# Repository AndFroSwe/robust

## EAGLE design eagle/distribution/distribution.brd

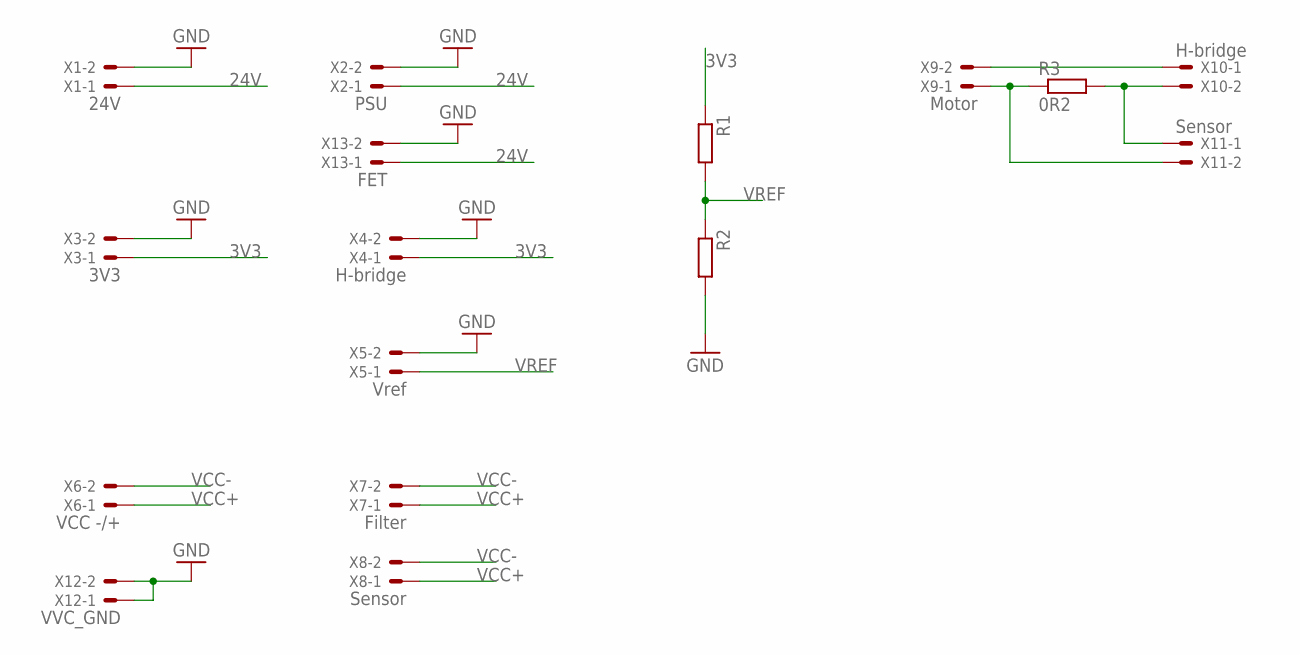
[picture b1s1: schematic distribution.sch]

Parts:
R1, R2: R-EU_0207/10; 0207/10
R3: 0R2; 0414/15
X1: 24V; 22-23-2021
X2: PSU; 22-23-2021
X3: 3V3; 22-23-2021
X4, X10: H-bridge; 22-23-2021
X5: Vref; 22-23-2021
X6: VCC -/+; 22-23-2021
X7: Filter; 22-23-2021
X8, X11: Sensor; 22-23-2021
X9: Motor; 22-23-2021
X12: VVC_GND; 22-23-2021
X13: FET; 22-23-2021

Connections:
3V3: R1.1, X3.1, X4.1
24V: X1.1, X2.1, X13.1
GND: R2.2, X1.2, X2.2, X3.2, X4.2, X5.2, X12.1, X12.2, X13.2
unnamed: R3.1, X9.1, X11.2
unnamed: R3.2, X10.2, X11.1
unnamed: X9.2, X10.1
VCC+: X6.1, X7.1, X8.1
VCC-: X6.2, X7.2, X8.2
VREF: R1.2, R2.1, X5.1

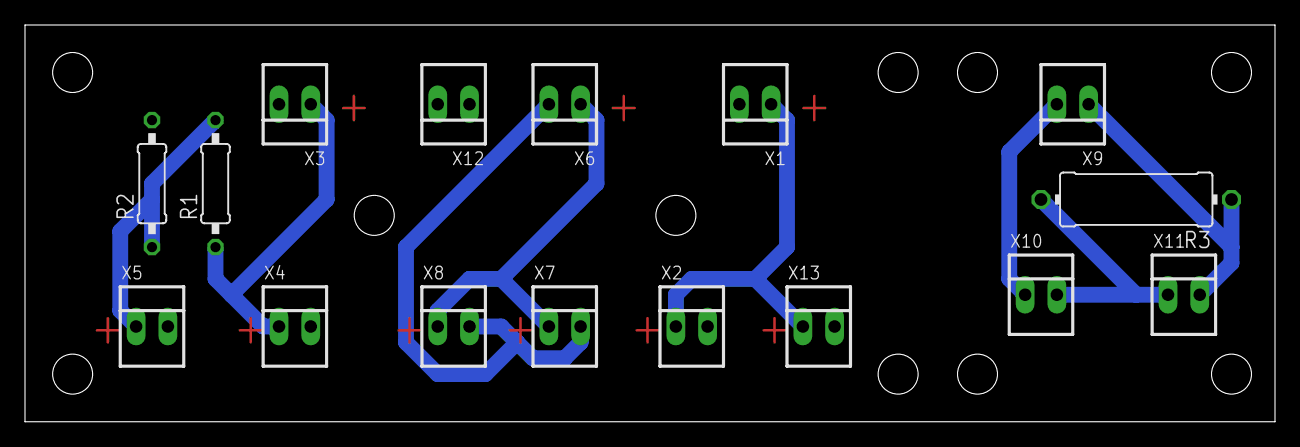
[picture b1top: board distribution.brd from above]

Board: 2 copper layers, 100.0 x 31.7 mm, 16 parts (0 on the bottom side), 9 nets.

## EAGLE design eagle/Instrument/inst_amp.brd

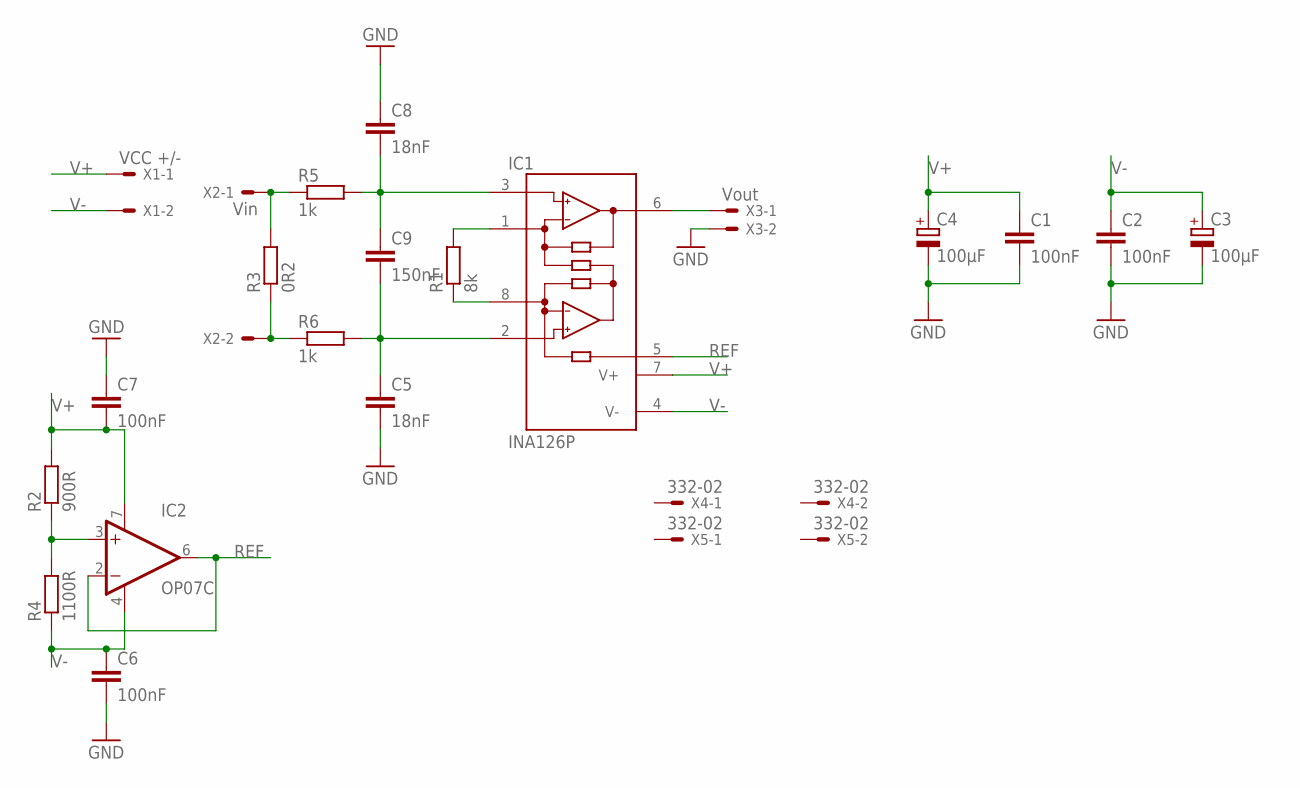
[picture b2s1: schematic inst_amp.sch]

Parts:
C1, C2, C6, C7: 100nF; C050-025X075
C3, C4: 100µF; E5-10,5
C5, C8: 18nF; C050-024X044
C9: 150nF; C050-025X075
IC1: INA126P; DIL08
IC2: OP07C; DIL08
R1: 8k; 0207/10
R2: 900R; 0207/10
R3: 0R2; 0414/15
R4: 1100R; 0207/10
R5, R6: 1k; 0207/10
X1: VCC +/-; 22-23-2021
X2: Vin; 22-23-2021
X3: Vout; 22-23-2021
X4, X5: 332-02

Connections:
GND: C1.2, C2.2, C3.-, C4.-, C5.2, C6.2, C7.1, C8.1, X3.2
unnamed: IC1.1 (RG), R1.2
unnamed: IC1.8 (RG), R1.1
unnamed: R3.1, R6.1, X2.2
unnamed: IC2.3 (+IN), R2.1, R4.2
unnamed: IC1.6 (OUT), X3.1
unnamed: C8.2, C9.1, IC1.3 (+IN), R5.2
unnamed: C5.1, C9.2, IC1.2 (-IN), R6.2
unnamed: R3.2, R5.1, X2.1
REF: IC1.5 (REF), IC2.2 (-IN), IC2.6 (OUT)
V+: C1.1, C4.+, C7.2, IC1.7 (V+), IC2.7 (V+), R2.2, X1.1
V-: C2.1, C3.+, C6.1, IC1.4 (V-), IC2.4 (V-), R4.1, X1.2

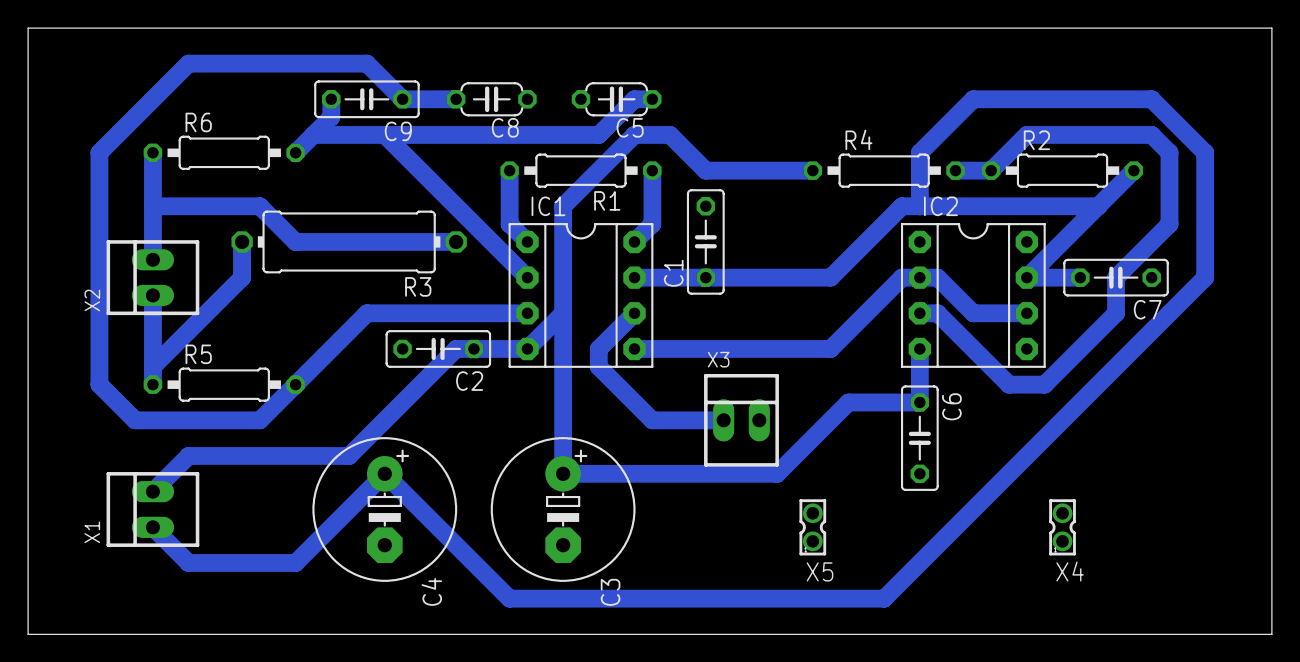
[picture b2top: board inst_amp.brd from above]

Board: 2 copper layers, 88.6 x 43.2 mm, 22 parts (0 on the bottom side), 12 nets.

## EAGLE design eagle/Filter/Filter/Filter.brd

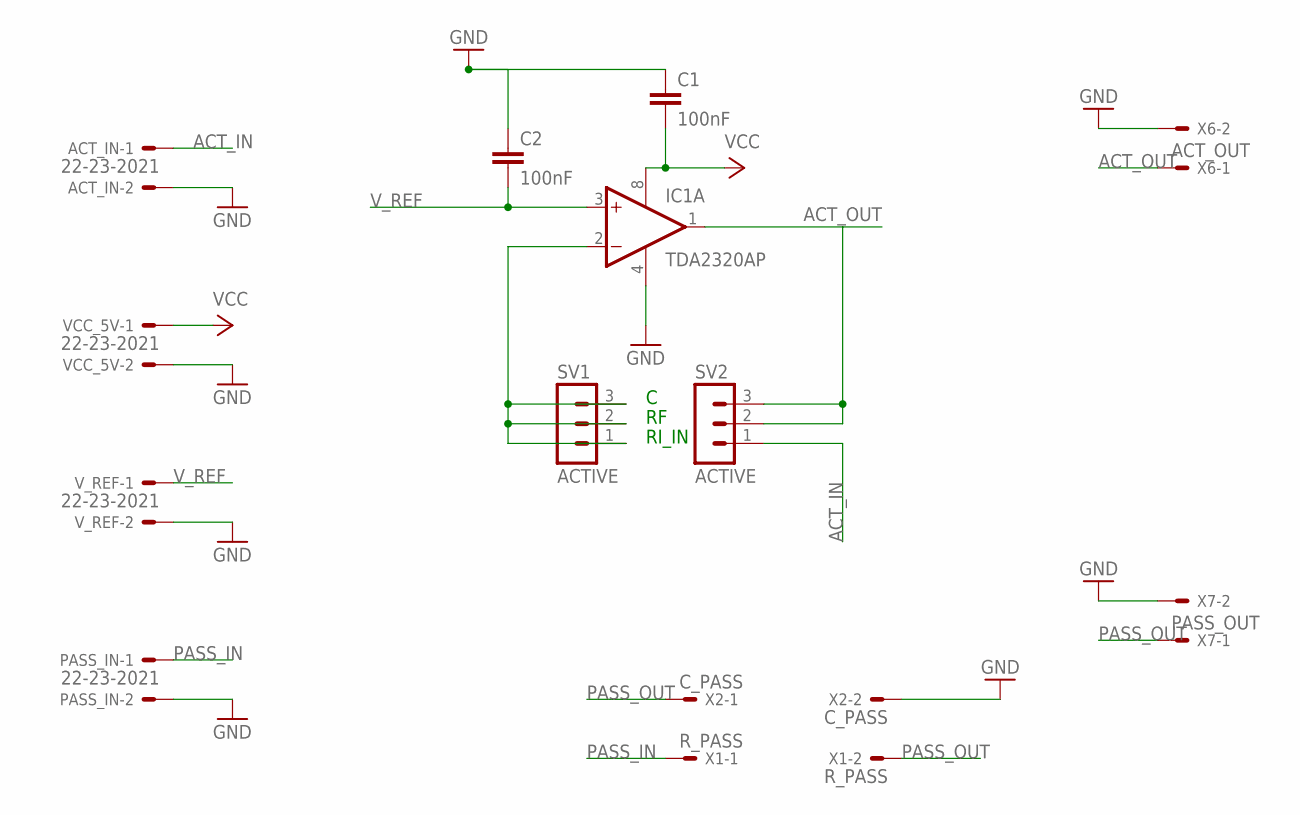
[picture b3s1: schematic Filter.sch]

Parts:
ACT_IN: 22-23-2021
C1, C2: 100nF; C5B3
IC1: TDA2320AP; DIL08
PASS_IN: 22-23-2021
SV1, SV2: ACTIVE; MA03-1
VCC_5V: 22-23-2021
V_REF: 22-23-2021
X1: R_PASS; 87758-0216
X2: C_PASS; 87758-0216
X6: ACT_OUT; 22-23-2021
X7: PASS_OUT; 22-23-2021

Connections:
ACT_IN: ACT_IN.1, SV2.1
ACT_OUT: IC1.1 (OUT), SV2.2, SV2.3, X6.1
GND: ACT_IN.2, C1.1, C2.1, IC1.4 (V-), PASS_IN.2, VCC_5V.2, V_REF.2, X2.2, X6.2, X7.2
unnamed: IC1.2 (-IN), SV1.1, SV1.2, SV1.3
PASS_IN: PASS_IN.1, X1.1
PASS_OUT: X1.2, X2.1, X7.1
VCC: C1.2, IC1.8 (V+), VCC_5V.1
V_REF: C2.2, IC1.3 (+IN), V_REF.1

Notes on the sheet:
RI_IN

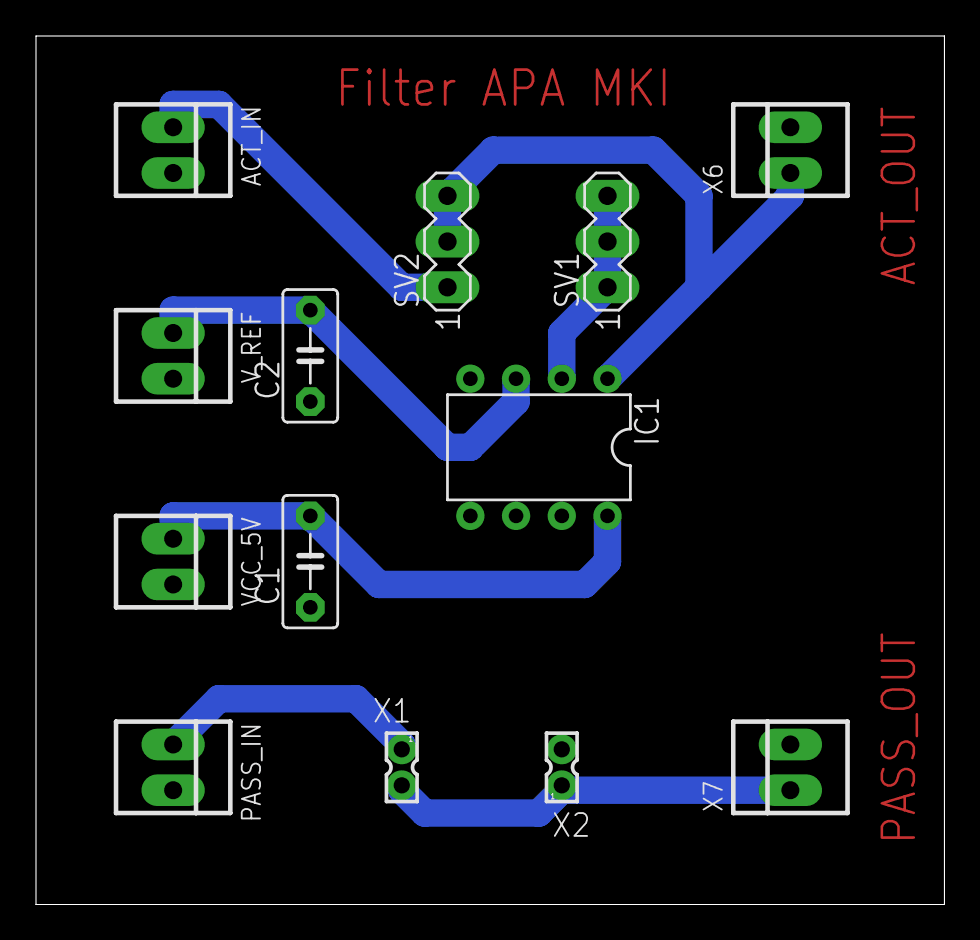
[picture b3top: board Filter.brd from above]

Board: 2 copper layers, 50.5 x 48.2 mm, 13 parts (0 on the bottom side), 8 nets.

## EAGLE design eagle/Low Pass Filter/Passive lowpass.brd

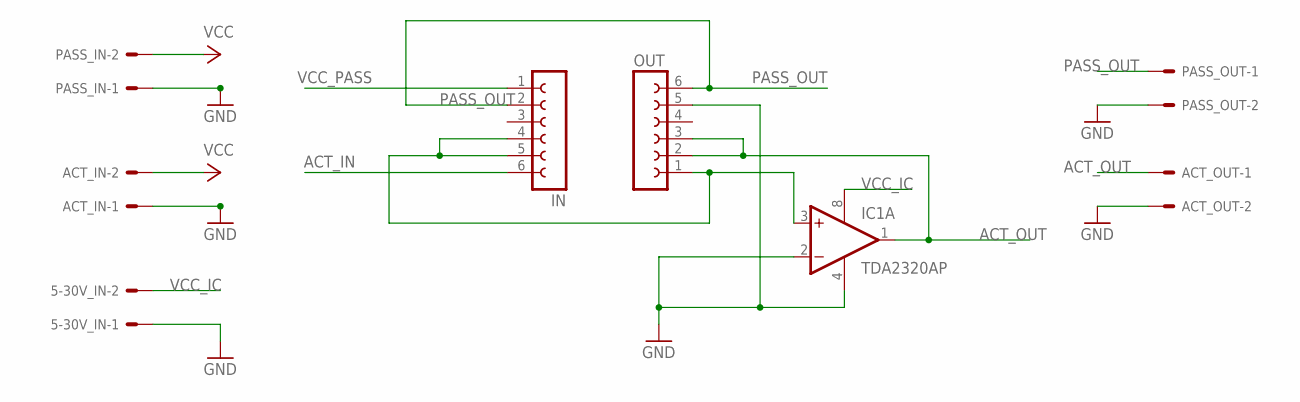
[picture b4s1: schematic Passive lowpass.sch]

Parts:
5-30V_IN: KK-156-2
ACT_IN: KK-156-2
ACT_OUT: KK-156-2
IC1: TDA2320AP; DIL08
IN: FE06W
OUT: FE06W
PASS_IN: KK-156-2
PASS_OUT: KK-156-2

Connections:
ACT_IN: IN.6
ACT_OUT: ACT_OUT.1, IC1.1 (OUT), OUT.2, OUT.3
GND: 5-30V_IN.1, ACT_IN.1, ACT_OUT.2, IC1.2 (-IN), IC1.4 (V-), OUT.5, PASS_IN.1, PASS_OUT.2
unnamed: IC1.3 (+IN), IN.4, IN.5, OUT.1
PASS_OUT: IN.2, OUT.6, PASS_OUT.1
VCC: PASS_IN.2
VCC_IC: 5-30V_IN.2, IC1.8 (V+)
VCC_PASS: ACT_IN.2, IN.1

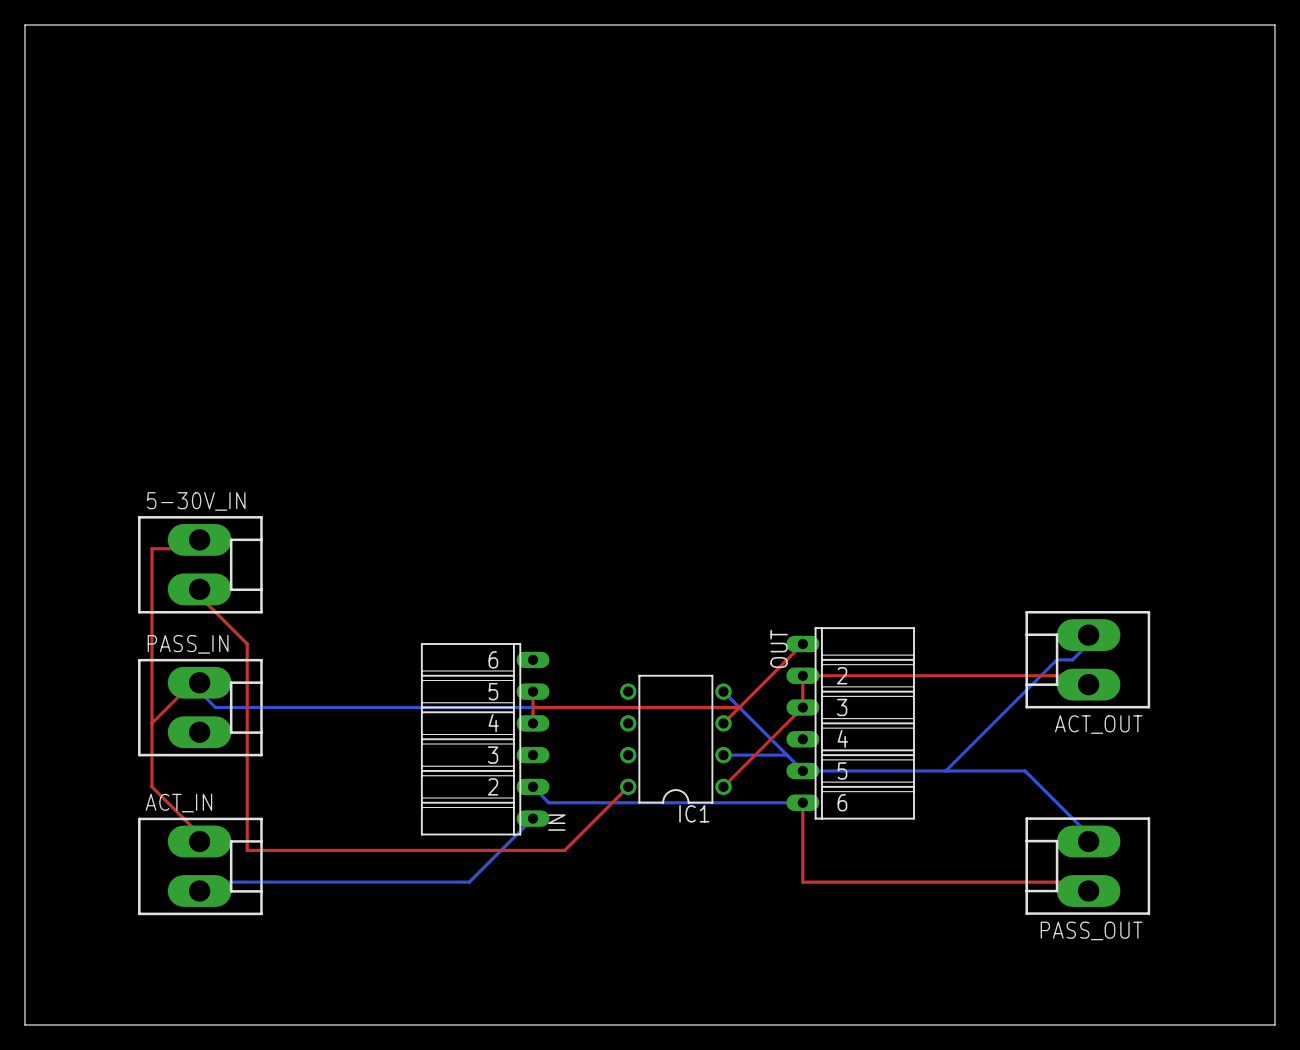
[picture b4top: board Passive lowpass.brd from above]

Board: 2 copper layers, 100.0 x 80.0 mm, 8 parts (0 on the bottom side), 6 nets.

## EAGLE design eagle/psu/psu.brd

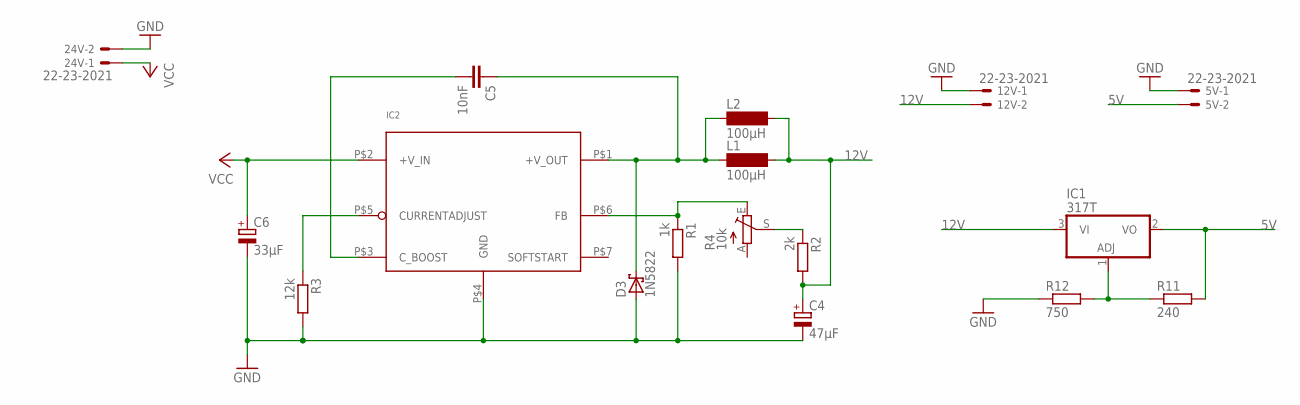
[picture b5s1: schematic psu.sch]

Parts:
5V, 12V, 24V: 22-23-2021
C4: 47µF; E2,5-5
C5: 10nF; C5B2.5
C6: 33µF; E2,5-5
D3: 1N5822; C4111-15
IC1: 317T; TO220H
IC2: LM2576-T05D; TO220-5_STAGGERED
L1, L2: 100µH; SD75
R1: 1k; 0207/10
R2: 2k; 0207/10
R3: 12k; 0207/10
R4: 10k; B25P
R11: 240; 0207/10
R12: 750; 0207/10

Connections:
5V: 5V.2, IC1.2 (VO), R11.2
12V: 12V.2, C4.+, IC1.3 (VI), L1.2, L2.2, R2.2
GND: 5V.1, 12V.1, 24V.2, C4.-, C6.-, D3.A, IC2.P$4 (GND), R1.2, R3.2, R12.1
unnamed: IC1.1 (ADJ), R11.1, R12.2
unnamed: R2.1, R4.S
unnamed: IC2.P$6 (FB), R1.1, R4.E
unnamed: C5.2, IC2.P$3 (C_BOOST)
unnamed: C5.1, D3.C, IC2.P$1 (+V_OUT), L1.1, L2.1
unnamed: IC2.P$5 (CURRENTADJUST), R3.1
VCC: 24V.1, C6.+, IC2.P$2 (+V_IN)

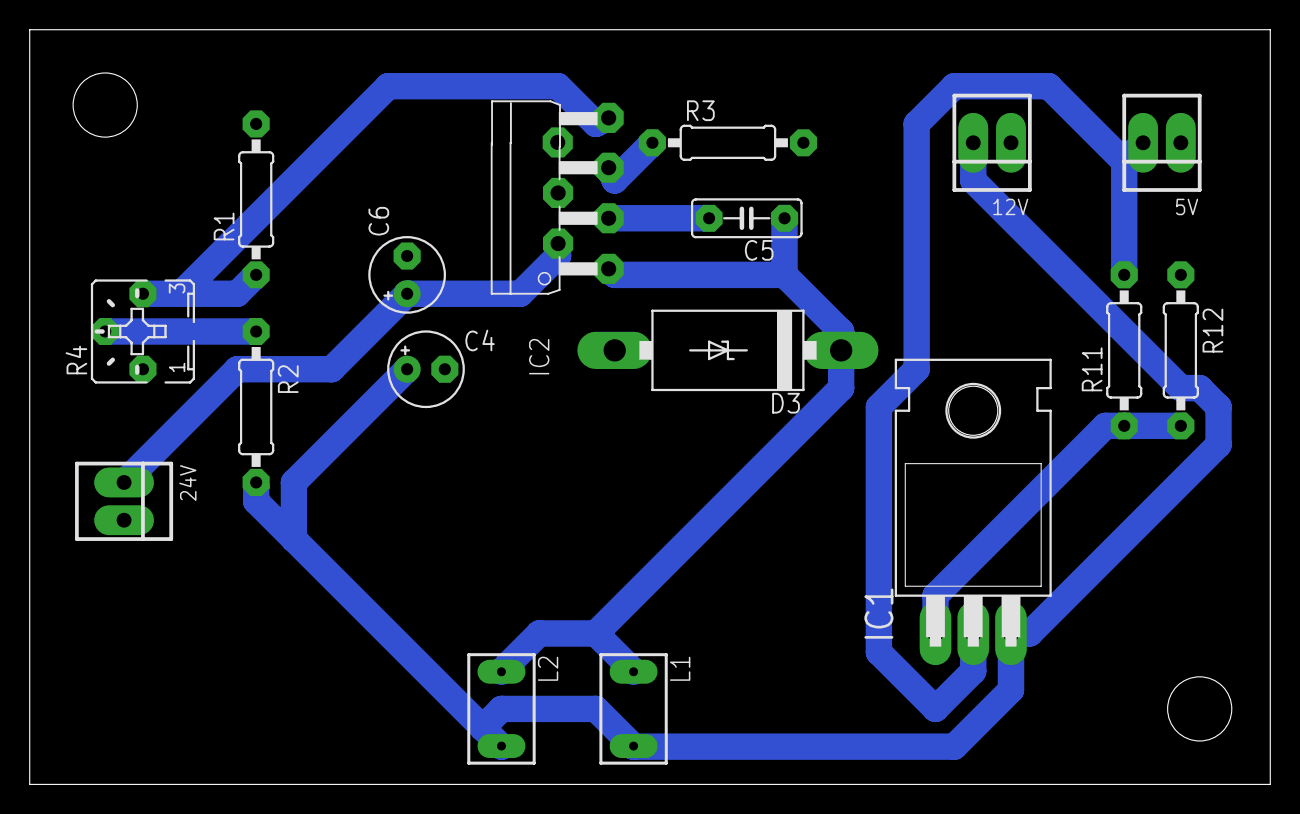
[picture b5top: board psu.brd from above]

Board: 2 copper layers, 83.5 x 50.8 mm, 17 parts (0 on the bottom side), 10 nets.

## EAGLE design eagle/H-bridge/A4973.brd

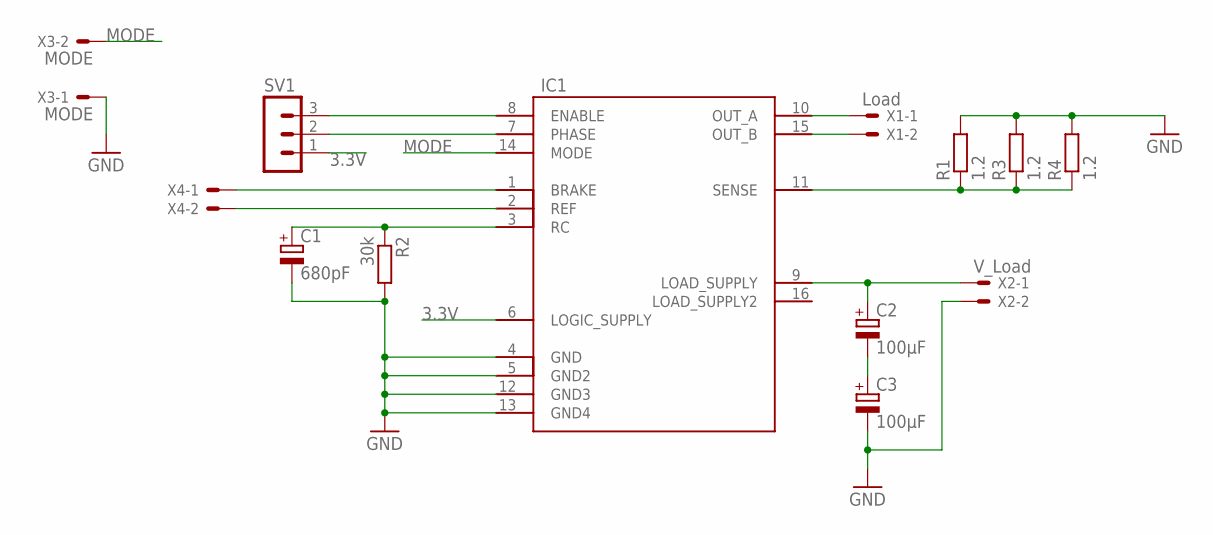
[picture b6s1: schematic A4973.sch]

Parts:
C1: 680pF; ETR4
C2, C3: 100µF; E5-13
IC1: A4973DIL; DIL16
R1, R3, R4: 1.2; 0207/10
R2: 30k; 0207/12
SV1: MA03-1
X1: Load; 22-23-2021
X2: V_Load; 22-23-2021
X3: MODE; 332-02
X4: 332-02

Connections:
3.3V: IC1.6 (LOGIC_SUPPLY), SV1.1
GND: C1.-, C3.-, IC1.4 (GND), IC1.5 (GND2), IC1.12 (GND3), IC1.13 (GND4), R1.2, R2.2, R3.2, R4.2, X2.2, X3.1
MODE: IC1.14 (MODE), X3.2
unnamed: IC1.8 (ENABLE), SV1.3
unnamed: IC1.7 (PHASE), SV1.2
unnamed: C2.-, C3.+
unnamed: IC1.10 (OUT_A), X1.1
unnamed: IC1.15 (OUT_B), X1.2
unnamed: IC1.11 (SENSE), R1.1, R3.1, R4.1
unnamed: C1.+, IC1.3 (RC), R2.1
unnamed: C2.+, IC1.9 (LOAD_SUPPLY), X2.1
unnamed: IC1.1 (BRAKE), X4.1
unnamed: IC1.2 (REF), X4.2

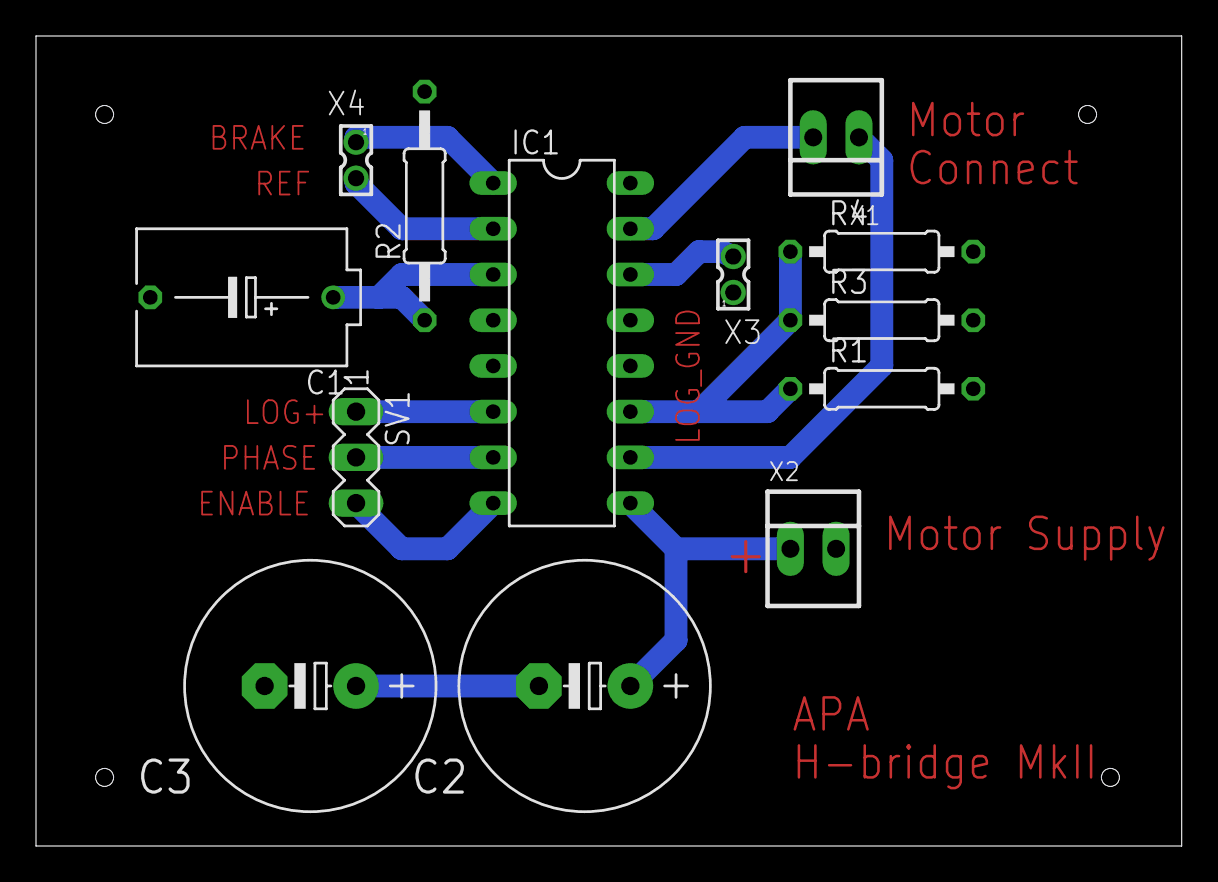
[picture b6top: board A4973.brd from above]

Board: 2 copper layers, 63.6 x 45.0 mm, 13 parts (0 on the bottom side), 13 nets.

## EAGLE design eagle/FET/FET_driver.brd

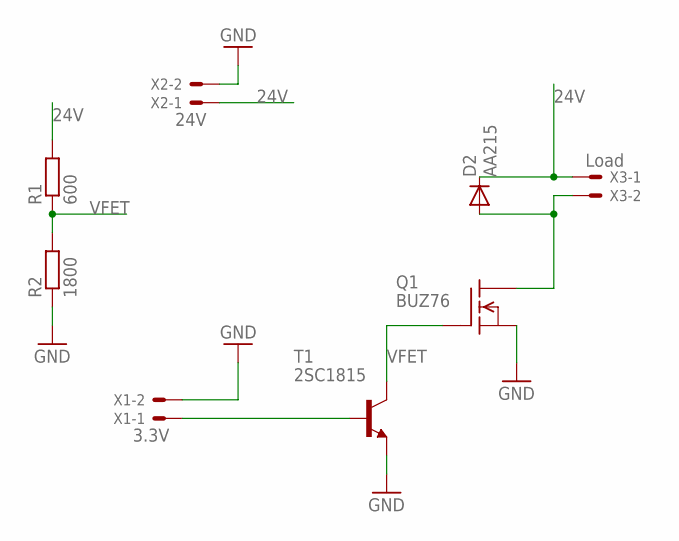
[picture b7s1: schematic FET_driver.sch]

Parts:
D2: AA215; DO07
Q1: BUZ76; TO220
R1: 600; 0207/10
R2: 1800; 0207/10
T1: 2SC1815; TO92-ECB
X1: 3.3V; 22-23-2021
X2: 24V; 22-23-2021
X3: Load; 22-23-2021

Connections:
24V: D2.C, R1.2, X2.1, X3.1
GND: Q1.3 (S), R2.1, T1.E, X1.2, X2.2
unnamed: D2.A, Q1.2 (D), X3.2
unnamed: T1.B, X1.1
VFET: Q1.1 (G), R1.1, R2.2, T1.C

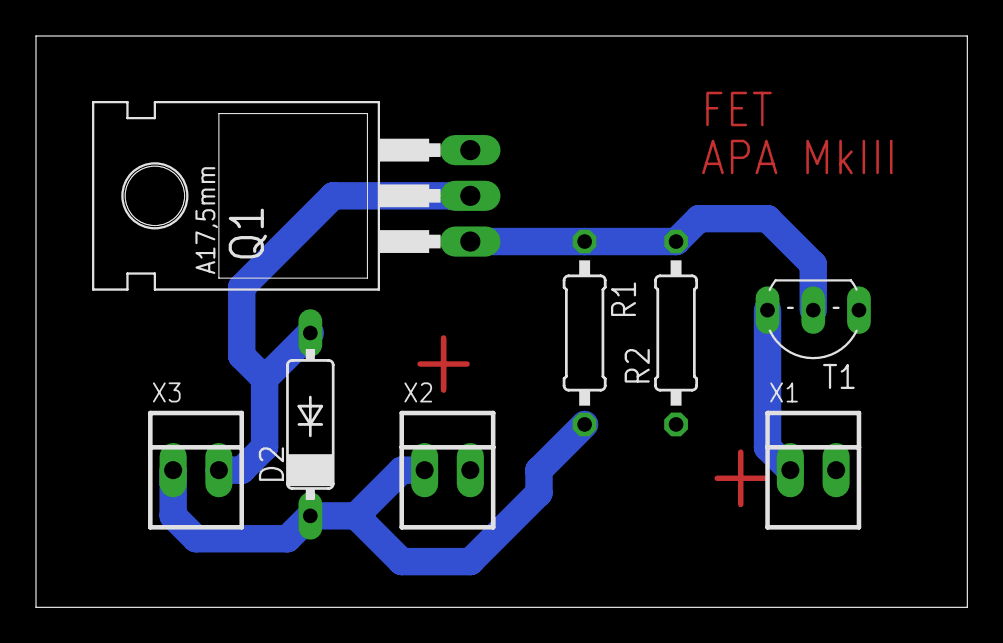
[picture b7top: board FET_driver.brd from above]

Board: 2 copper layers, 51.7 x 31.7 mm, 8 parts (0 on the bottom side), 5 nets.

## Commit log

2015-11-20 Initial commit (sort of). Labb 1 and 2 done
2015-11-20 Added lab files
2015-11-20 Added component script
2015-11-20 Added matlab file for active filter
2015-11-20 Added low pass filter
2015-11-23 Refined matlab script, gives wierd curves
2015-11-23 More experimenting with matlab
2015-11-24 Added filter pcb
2015-11-25 Fixed filter files, fixed molex on eagle board
2015-11-26 Changes to mbed and matlab
2015-11-26 We understand filters now
2015-11-30 Fixed instrument amplifier. Left to do: Add voltage reference 1.5 v via an op amp
2015-12-01 PCB design done
2015-12-01 Added data sheet for op07
2015-12-03 Added lo pass filter
2015-12-03 Labb4 done
2015-12-07 ADC is activated and PWM works
2015-12-09 P controller implemented
2015-12-09 Regulations (kinda) works
2015-12-10 Labb 5 done. Only used P controller. IT'S DONE.
